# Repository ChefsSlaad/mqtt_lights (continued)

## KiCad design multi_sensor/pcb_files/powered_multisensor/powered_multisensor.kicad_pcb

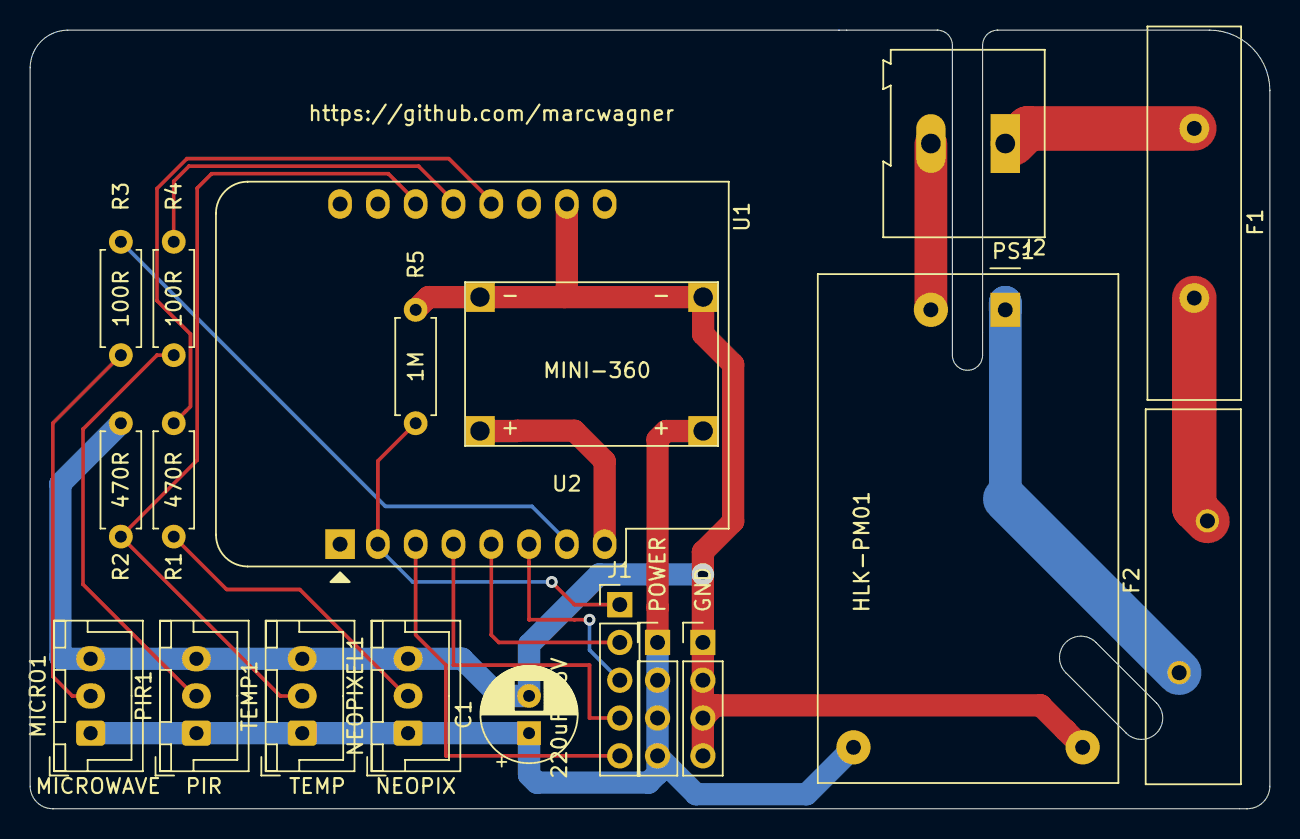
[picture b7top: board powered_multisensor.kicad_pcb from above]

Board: 2 copper layers, 83.3 x 52.3 mm, 19 parts (0 on the bottom side), 19 nets.

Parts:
C1: 220uF 16V; CP_Radial_D6.3mm_P2.50mm
F1: 300mA Fuse; Fuse_Littelfuse-LVR200
F2: 77C Thermal Fuse; Fuse_BelFuse_0ZRE0200FF_L24.9mm_W6.1mm
GND: Conn_01x04_Male; PinHeader_1x04_P2.54mm_Vertical
J1: Conn_01x05_Male; PinHeader_1x05_P2.54mm_Vertical
J2: Screw_Terminal_01x02; TerminalBlock_Altech_AK300-2_P5.00mm
MICRO1: Conn_01x03_Female; JST_XH_B3B-XH-A_1x03_P2.50mm_Vertical
NEOPIXEL1: Conn_01x03_Female; JST_XH_B3B-XH-A_1x03_P2.50mm_Vertical
PIR1: Conn_01x03_Female; JST_XH_B3B-XH-A_1x03_P2.50mm_Vertical
POWER: Conn_01x04_Male; PinHeader_1x04_P2.54mm_Vertical
PS1: HLK-PM01; Converter_ACDC_HiLink_HLK-PMxx
R1, R2: 470R; R_Axial_DIN0207_L6.3mm_D2.5mm_P7.62mm_Horizontal
R3, R4: 100R; R_Axial_DIN0207_L6.3mm_D2.5mm_P7.62mm_Horizontal
R5: 1M; R_Axial_DIN0207_L6.3mm_D2.5mm_P7.62mm_Horizontal
TEMP1: Conn_01x03_Female; JST_XH_B3B-XH-A_1x03_P2.50mm_Vertical
U1: WeMos_D1_mini; WEMOS_D1_mini_light
U2: MINI-360; MINI_360_DC-DC_BUCK_CONVERTER

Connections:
+3V3: U1.8, U2.3
+5V: C1.1, MICRO1.1, NEOPIXEL1.1, PIR1.1, POWER.1, POWER.2, POWER.3, POWER.4, PS1.4, TEMP1.1, U2.1
/ANALOG: J1.1, R5.2, U1.2
/GPIO12: J1.2, U1.5
/GPIO13: J1.3, U1.6
/GPIO14: J1.4, U1.4
/GPIO16: J1.5, U1.3
/Live: F2.1, PS1.1
/MICRO: R3.2, U1.7
/NEOPIXEL: R1.2, U1.12
/Neutral: J2.2, PS1.2
/PIR: R4.2, U1.13
/TEMP_SENSOR: R2.2, TEMP1.2, U1.14
GND: C1.2, GND.1, GND.2, GND.3, GND.4, MICRO1.3, NEOPIXEL1.3, PIR1.3, PS1.3, R2.1, R5.1, TEMP1.3, U1.10, U2.2, U2.4
unnamed: F1.1, J2.1
unnamed: F1.2, F2.2
unnamed: MICRO1.2, R3.1
unnamed: NEOPIXEL1.2, R1.1
unnamed: PIR1.2, R4.1

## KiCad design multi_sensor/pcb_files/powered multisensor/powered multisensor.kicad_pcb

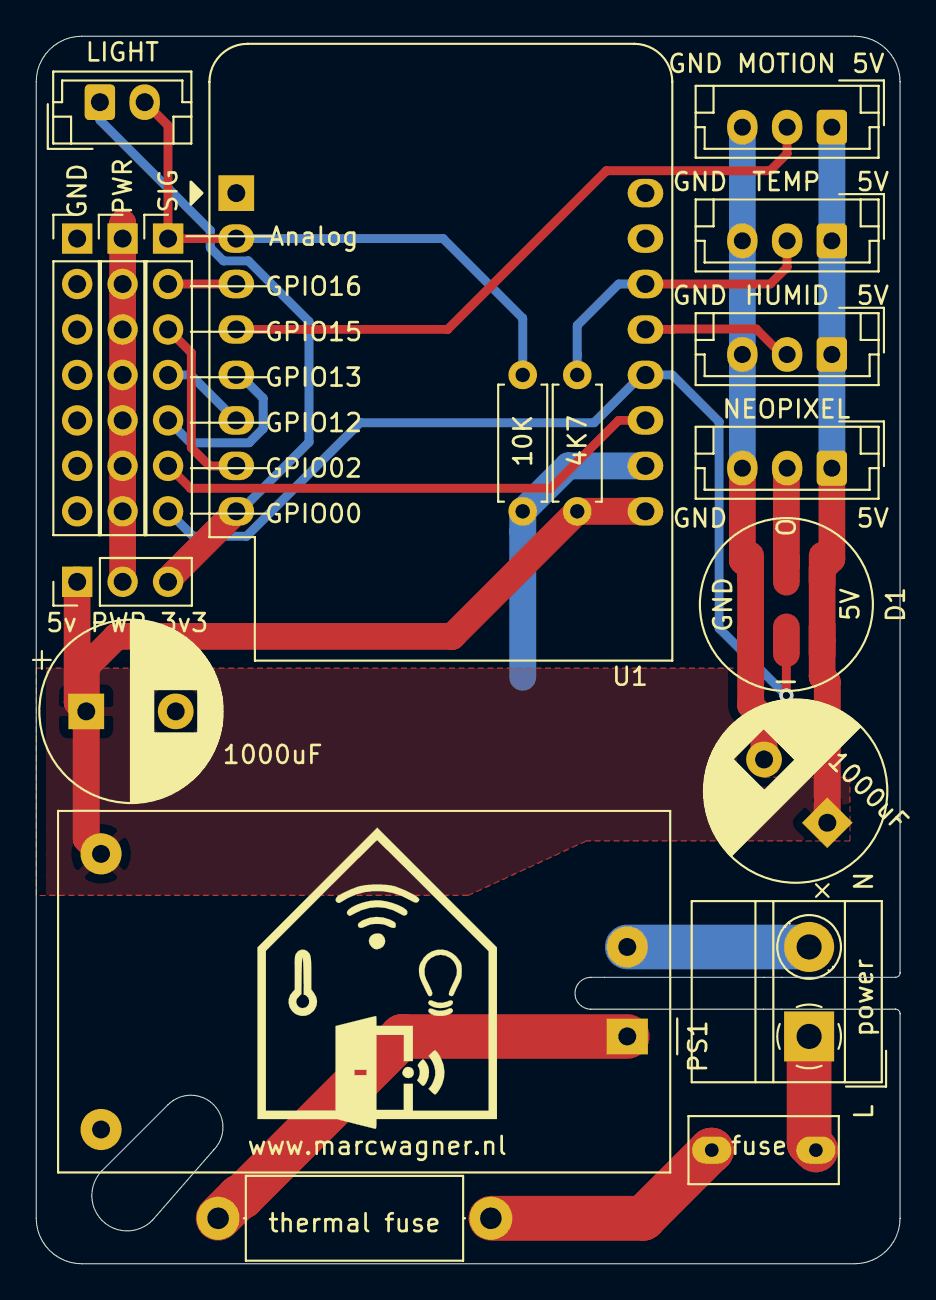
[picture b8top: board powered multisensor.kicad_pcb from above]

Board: 2 copper layers, 48.3 x 68.6 mm, 19 parts (0 on the bottom side), 19 nets.

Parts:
4K7: 4K7; R_Axial_DIN0207_L6.3mm_D2.5mm_P7.62mm_Horizontal
5v PWR 3v3: Conn_01x03_Male; PinHeader_1x03_P2.54mm_Vertical
10K: 10K; R_Axial_DIN0207_L6.3mm_D2.5mm_P7.62mm_Horizontal
1000uF: 1000uF; CP_Radial_D10.0mm_P5.00mm
1000uF#2: CP; CP_Radial_D10.0mm_P5.00mm
D1: WS2812B; neopixel_pcb
GND: Conn_01x07_Male; PinHeader_1x07_P2.54mm_Vertical
HUMID: Conn_01x03_Male; JST_EH_B3B-EH-A_1x03_P2.50mm_Vertical
L     power     N: Screw_Terminal_01x02; TerminalBlock_MetzConnect_Type011_RT05502HBWC_1x02_P5.00mm_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
LIGHT: Conn_01x02_Male; JST_EH_B2B-EH-A_1x02_P2.50mm_Vertical
MOTION: Conn_01x03_Male; JST_EH_B3B-EH-A_1x03_P2.50mm_Vertical
NEOPIXEL: Conn_01x03_Male; JST_EH_B3B-EH-A_1x03_P2.50mm_Vertical
PS1: HLK-PM01; Converter_ACDC_HiLink_HLK-PMxx
PWR: Conn_01x07_Male; PinHeader_1x07_P2.54mm_Vertical
SIG: Conn_01x07_Male; PinHeader_1x07_P2.54mm_Vertical
TEMP: Conn_01x03_Male; JST_EH_B3B-EH-A_1x03_P2.50mm_Vertical
U1: WeMos_D1_mini; WEMOS_D1_mini_light
fuse: fuse 250V 2A; slow blow fuse
thermal fuse: Thermistor; R_Axial_DIN0414_L11.9mm_D4.5mm_P15.24mm_Horizontal

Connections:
+3V3: 5v PWR 3v3.3, LIGHT.1, U1.8
+5V: 4K7.1, 5v PWR 3v3.1, 1000uF.1, 1000uF#2.1, D1.1, HUMID.1, MOTION.1, NEOPIXEL.1, PS1.4, TEMP.1, U1.9
/a_light: 10K.1, LIGHT.2, SIG.1, U1.2
/gpi015: SIG.3, U1.7
/gpio02: SIG.6, U1.11
/gpio12: SIG.5, U1.5
/gpio13: SIG.4, U1.6
/gpio16: SIG.2, U1.3
/pwr_select: 5v PWR 3v3.2, PWR.1, PWR.2, PWR.3, PWR.4, PWR.5, PWR.6, PWR.7
/s_humidity: HUMID.2, U1.13
/s_motion: MOTION.2, U1.4
/s_neopixel: D1.4, SIG.7, U1.12
/s_temperature: 4K7.2, TEMP.2, U1.14
GND: 10K.2, 1000uF.2, 1000uF#2.2, D1.3, GND.1, GND.2, GND.3, GND.4, GND.5, GND.6, GND.7, HUMID.3, MOTION.3, NEOPIXEL.3, PS1.3, TEMP.3, U1.10
unnamed: D1.2, NEOPIXEL.2
unnamed: fuse.1, thermal fuse.1
unnamed: L power N.1, fuse.2
unnamed: L power N.2, PS1.2
unnamed: PS1.1, thermal fuse.2

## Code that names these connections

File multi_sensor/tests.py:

from machine import Pin, Timer
from time import sleep, sleep_ms, localtime, time
from neopixel import NeoPixel
from onewire import OneWire
from ds18x20 import DS18X20


class multisensor:
    def __init__(self, motion_pin, micro_pin, pixel_pin, pixels, temp_pin):
        self.motion = 'OFF'
        self.motion_timer = Timer(-1)
        self.temp_timer = Timer(-2)
        self.temperature = None
        self.one_wire = DS18X20(OneWire(Pin(temp_pin)))
        self.temp_sensor = None # initiated in function temp_sensor
        self.micro_sensor = Pin(micro_pin, Pin.IN)
        self.micro_sensor.irq(handler = self.micro_high, trigger = Pin.IRQ_RISING)
        self.motion_sensor = Pin(motion_pin, Pin.IN)
        self.motion_sensor.irq(handler = self.motion_high, trigger = Pin.IRQ_RISING)
        self.pixels = NeoPixel(Pin(pixel_pin), pixels)
        self.lastmotion = time()

        self.temp_sensor_init()

    def temp_sensor_init(self):
        self.temp_sensor = self.one_wire.scan()[0]
        sleep_ms(750)
        self.read_temperature()
        self.temp_timer.init(mode = Timer.PERIODIC, period = 10000, callback = self.read_temperature)

    def setcolor(self, color: tuple, pixels: tuple = ()):
        '''set the color of the pixel(s) to a certain color'''
        if pixels == (): pixels = range(self.pixels.n)
        for i in pixels:
            self.pixels[i] = color
        self.pixels.write()

    def read_temperature(self, sensor = None):
        self.one_wire.convert_temp()
        self.temperature = round(self.one_wire.read_temp(self.temp_sensor),1) #read temp and round to 1 digit
        print('{} temperature {}'.format(self.__read_time(), self.temperature))

    def motion_high(self, sensor):
        self.motion = 'ON'
        self.lastmotion = time()
        self.motion_timer.init(mode=Timer.ONE_SHOT, period = 30000, callback = self.sensor_timeout)
        print('{} pir detected. Value {}'.format(self.__read_time(), self.motion))
        self.setcolor((0,255,0))

    def micro_high(self, sensor):
        self.motion = 'ON'
        self.motion_timer.init(mode=Timer.ONE_SHOT, period = 30000, callback = self.sensor_timeout)
        print('{} micro detected. Value {}'.format(self.__read_time(), self.motion))
        self.setcolor((0,0,255))

    def sensor_timeout(self, selftimer):
        self.motion = 'OFF'
        self.setcolor((255,0,0))

    def __read_time(self):
        t = localtime()
        return '{:0<2}:{:0<2}:{:0<2}'.format(t[3],t[4], t[5])


mysensor = multisensor(motion_pin = 4, micro_pin = 15, pixel_pin = 0, pixels = 1, temp_pin = 5)

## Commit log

2017-04-18 bugfixes
    refactored most of the code to get rid of a 'max recursion depth' error. It works now
2017-05-02 updated main.py and added the pcb gerber file
2017-12-13 added led switches files
2018-06-05 minor updates
2018-06-09 modules - wifi
2018-06-18 modules
2018-06-21 syncing
2018-06-24 finalised modules, config
2018-07-09 added functions for 2 seperate led units
2018-08-28 updating modules
2018-09-21 working on led strip controller
2018-09-22 squashing bugs
2018-09-22 minor tweaks
2018-11-05 start with tests
2018-11-06 added tests
2018-11-14 added 2 more test cases and some bugfixes
2018-11-15 bug in test fixed
2018-11-15 usability & speed
2018-11-15 initial testset
2018-11-17 updates from tests
2018-11-17 small updates in test
2018-11-18 led devices update
2018-11-25 finals on lights modules
2019-02-08 syncing some old stuff
2019-02-09 wrote unittests for the logger module
2019-02-10 removed logfile as logging is moved to mqtt
2019-02-10 removed pin2 as a validpin updated docstrings on rgb_hsv
2019-02-17 added binary sensor unit tests
2019-02-19 __init__ method accept a config dict rather than individual parameters
2019-03-01 many updates to the modules
2019-04-08 some overhaul to main loop
2019-11-22 updating
2020-02-15 updated pcb and logo
2020-04-01 updating pcb schematics
2020-05-08 created pcb for powered multisensor
2020-06-28 new pcbs for robo-car
2023-05-14 Create dir
2023-05-14 update 12v relay pcb
2023-05-15 better files
